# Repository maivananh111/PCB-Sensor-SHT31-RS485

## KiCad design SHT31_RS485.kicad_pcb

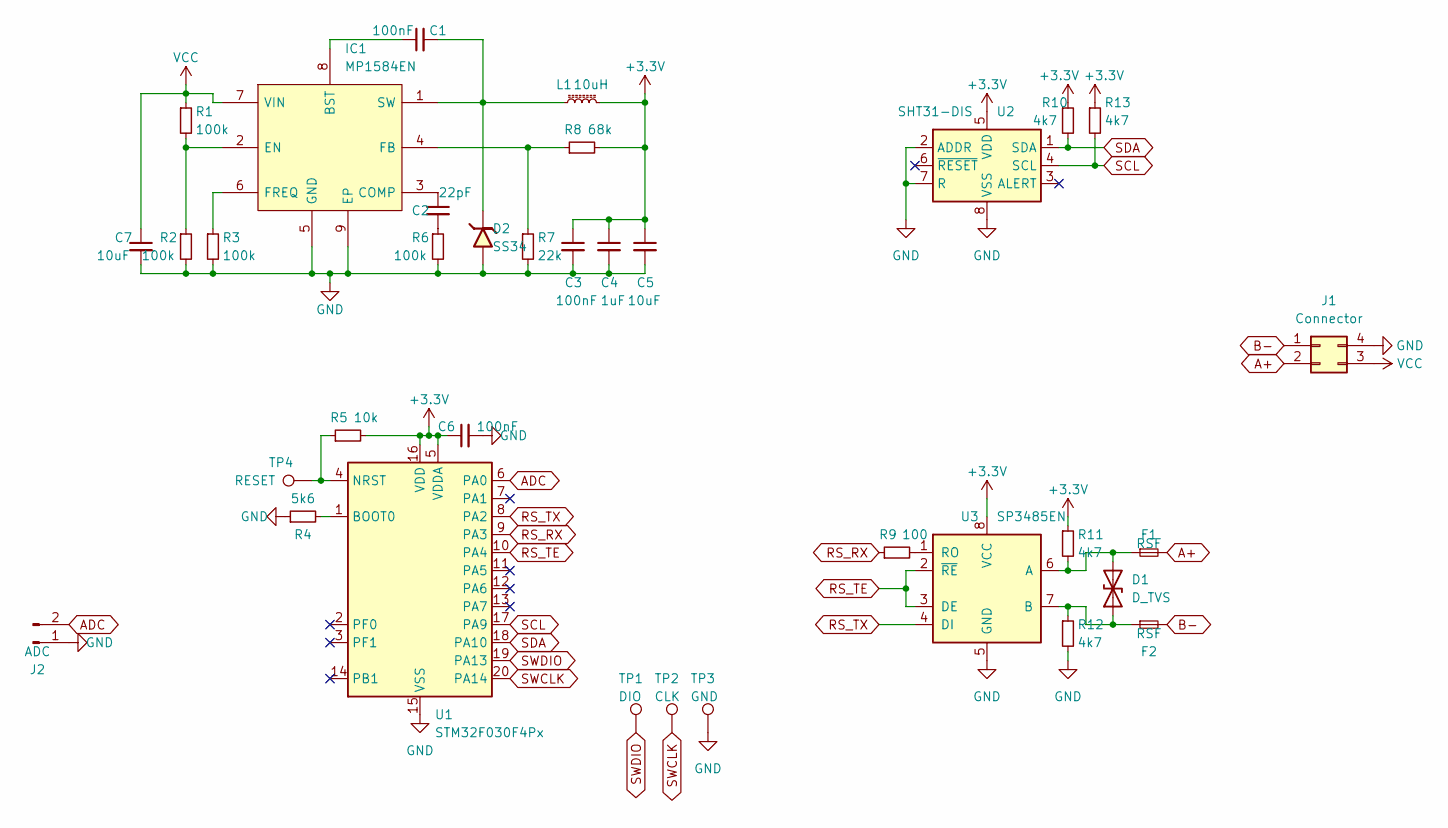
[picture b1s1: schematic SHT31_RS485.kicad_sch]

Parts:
C1, C3, C6: 100nF; C_0603_1608Metric
C2: 22pF; C_0603_1608Metric
C4: 1uF; C_1206_3216Metric
C5, C7: 10uF; C_1206_3216Metric
D1: D_TVS; D_SMA
D2: SS34; D_SMA
F1, F2: RSF; Fuse_1206_3216Metric
IC1: MP1584EN; SOIC-8-1EP_3.9x4.9mm_P1.27mm_EP2.29x3mm
J1: Connector; Conn_02x02_Horizontal_2Layer
J2: ADC; JST_GH_BM02B-GHS-TBT_1x02-1MP_P1.25mm_Vertical
L1: 10uH; L_Bourns_SRN6045TA
R1, R2, R3, R6: 100k; R_0603_1608Metric
R4: 5k6; R_0603_1608Metric
R5: 10k; R_0603_1608Metric
R7: 22k; R_0603_1608Metric
R8: 68k; R_0603_1608Metric
R9: 100; R_0603_1608Metric
R10, R11, R12, R13: 4k7; R_0603_1608Metric
TP1: DIO; TestPoint_Pad_D1.5mm
TP2: CLK; TestPoint_Pad_D1.5mm
TP3: GND; TestPoint_Pad_D1.5mm
TP4: RESET; TestPoint_Pad_D1.5mm
U1: STM32F030F4Px; TSSOP-20_4.4x6.5mm_P0.65mm
U2: SHT31-DIS; Sensirion_DFN-8-1EP_2.5x2.5mm_P0.5mm_EP1.1x1.7mm
U3: SP3485EN; SOIC-8_3.9x4.9mm_P1.27mm

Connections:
+3.3V: C3.1, C4.1, C5.1, C6.1, L1.2, R5.2, R8.2, R10.1, R11.1, R13.1, U1.5 (VDDA), U1.16 (VDD), U2.5 (VDD), U3.8 (VCC)
A+: F1.2, J1.2
ADC: J2.2, U1.6 (PA0)
B-: F2.2, J1.1
GND: C3.2, C4.2, C5.2, C6.2, C7.2, D2.2, IC1.5 (GND), IC1.9 (EP), J1.4, J2.1, R2.2, R3.2, R4.1, R6.2, R7.2, R12.2, TP3.1, U1.15 (VSS), U2.2 (ADDR), U2.7 (R), U2.8 (VSS), U2.9 (VSS), U3.5 (GND)
unnamed: C2.2, R6.1
unnamed: D1.1 (A1), F2.1, R12.1, U3.7 (B)
unnamed: D1.2 (A2), F1.1, R11.2, U3.6 (A)
unnamed: C1.1, IC1.8 (BST)
unnamed: C2.1, IC1.3 (COMP)
unnamed: IC1.2 (EN), R1.2, R2.1
unnamed: IC1.4 (FB), R7.1, R8.1
unnamed: IC1.6 (FREQ), R3.1
unnamed: C1.2, D2.1, IC1.1 (SW), L1.1
unnamed: R4.2, U1.1 (BOOT0)
unnamed: R5.1, TP4.1, U1.4 (NRST)
unnamed: R9.2, U3.1 (RO)
RS_RX: R9.1, U1.9 (PA3)
RS_TE: U1.10 (PA4), U3.2 (~RE), U3.3 (DE)
RS_TX: U1.8 (PA2), U3.4 (DI)
SCL: R13.2, U1.17 (PA9), U2.4 (SCL)
SDA: R10.2, U1.18 (PA10), U2.1 (SDA)
SWCLK: TP2.1, U1.20 (PA14)
SWDIO: TP1.1, U1.19 (PA13)
VCC: C7.1, IC1.7 (VIN), J1.3, R1.1

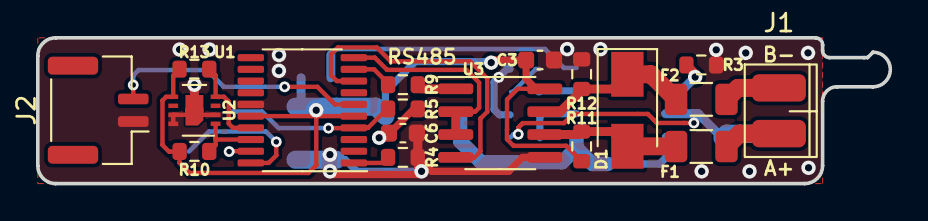
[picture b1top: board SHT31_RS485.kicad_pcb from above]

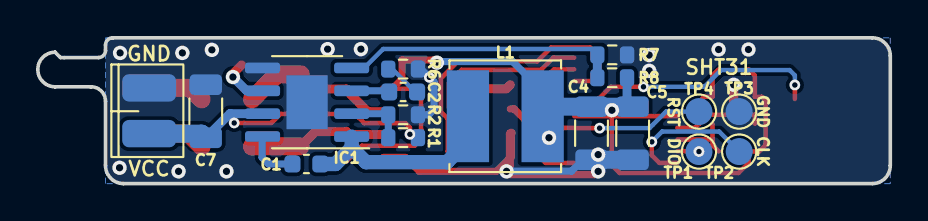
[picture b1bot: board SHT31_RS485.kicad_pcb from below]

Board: 2 copper layers, 47.4 x 8.1 mm, 34 parts (16 on the bottom side), 25 nets.

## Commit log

2023-02-05 Upload project file.
2023-04-14 Add MP1584EN Diose.
